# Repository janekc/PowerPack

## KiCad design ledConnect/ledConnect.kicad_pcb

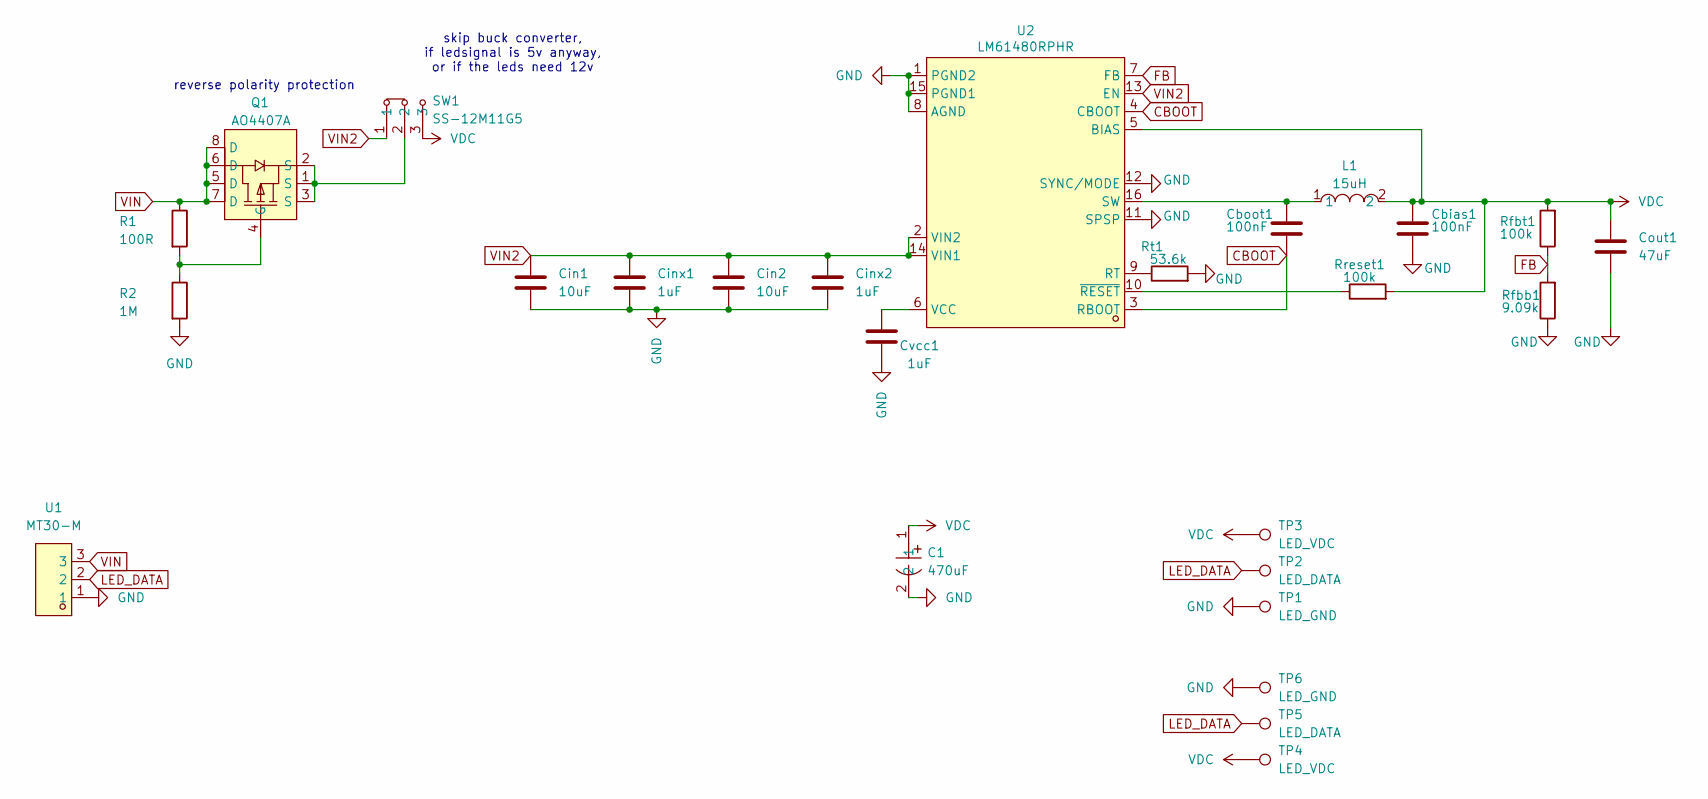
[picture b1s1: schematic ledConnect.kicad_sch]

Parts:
C1: 470uF; CAP-TH_BD10.0-P5.00-D0.6-FD; LCSC Part C2688262
Cbias1: 100nF
Cboot1: 100nF; C_0603_1608Metric_Pad1.08x0.95mm_HandSolder
Cin1, Cin2: 10uF; C_0603_1608Metric_Pad1.08x0.95mm_HandSolder
Cinx1, Cinx2: 1uF; C_0603_1608Metric_Pad1.08x0.95mm_HandSolder
Cout1: 47uF; C_1210_3225Metric_Pad1.33x2.70mm_HandSolder
Cvcc1: 1uF; C_0603_1608Metric_Pad1.08x0.95mm_HandSolder
L1: 15uH; IND-SMD_L13.5-W12.6; LCSC Part C2847574
Q1: AO4407A; SOIC-8_L4.9-W3.9-P1.27-LS6.0-BL; LCSC Part C16072
R1: 100R; R_0603_1608Metric_Pad0.98x0.95mm_HandSolder
R2: 1M; R_0603_1608Metric_Pad0.98x0.95mm_HandSolder
Rfbb1: 9.09k; R_0603_1608Metric_Pad0.98x0.95mm_HandSolder
Rfbt1: 100k; R_0603_1608Metric_Pad0.98x0.95mm_HandSolder
Rreset1: 100k; R_0603_1608Metric_Pad0.98x0.95mm_HandSolder
Rt1: 53.6k; R_0603_1608Metric_Pad0.98x0.95mm_HandSolder
SW1: SS-12M11G5; SW-TH_XKB_SS-12M11XX; LCSC Part C2879839
TP1, TP6: LED_GND; TestPoint_Pad_2.5x2.5mm
TP2, TP5: LED_DATA; TestPoint_Pad_2.5x2.5mm
TP3, TP4: LED_VDC; TestPoint_Pad_2.5x2.5mm
U1: MT30-M; CONN-TH_MT30-M; LCSC Part C99903
U2: LM61480RPHR; VQFN-16_L4.5-W3.5-P0.50-TL_TI_RPH; LCSC Part C3198089

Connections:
CBOOT: Cboot1.2, U2.3 (RBOOT), U2.4 (CBOOT)
FB: Rfbb1.2, Rfbt1.1, U2.7 (FB)
GND: C1.2, Cbias1.2, Cin1.2, Cin2.2, Cinx1.2, Cinx2.2, Cout1.2, Cvcc1.2, R2.2, Rfbb1.1, Rt1.2, TP1.1, TP6.1, U1.1, U2.1 (PGND2), U2.8 (AGND), U2.11 (SPSP), U2.12 (SYNC/MODE), U2.15 (PGND1)
LED_DATA: TP2.1, TP5.1, U1.2
unnamed: Q1.4 (G), R1.2, R2.1
unnamed: Q1.1 (S), Q1.2 (S), Q1.3 (S), SW1.2
unnamed: Rt1.1, U2.9 (RT)
unnamed: Cboot1.1, L1.1, U2.16 (SW)
unnamed: Cvcc1.1, U2.6 (VCC)
unnamed: Rreset1.1, U2.10 (~RESET)
VDC: C1.1, Cbias1.1, Cout1.1, L1.2, Rfbt1.2, Rreset1.2, SW1.3, TP3.1, TP4.1, U2.5 (BIAS)
VIN: Q1.5 (D), Q1.6 (D), Q1.7 (D), Q1.8 (D), R1.1, U1.3
VIN2: Cin1.1, Cin2.1, Cinx1.1, Cinx2.1, SW1.1, U2.2 (VIN2), U2.13 (EN), U2.14 (VIN1)

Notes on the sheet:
skip buck converter, if ledsignal is 5v anyway, or if the leds need 12v
reverse polarity protection

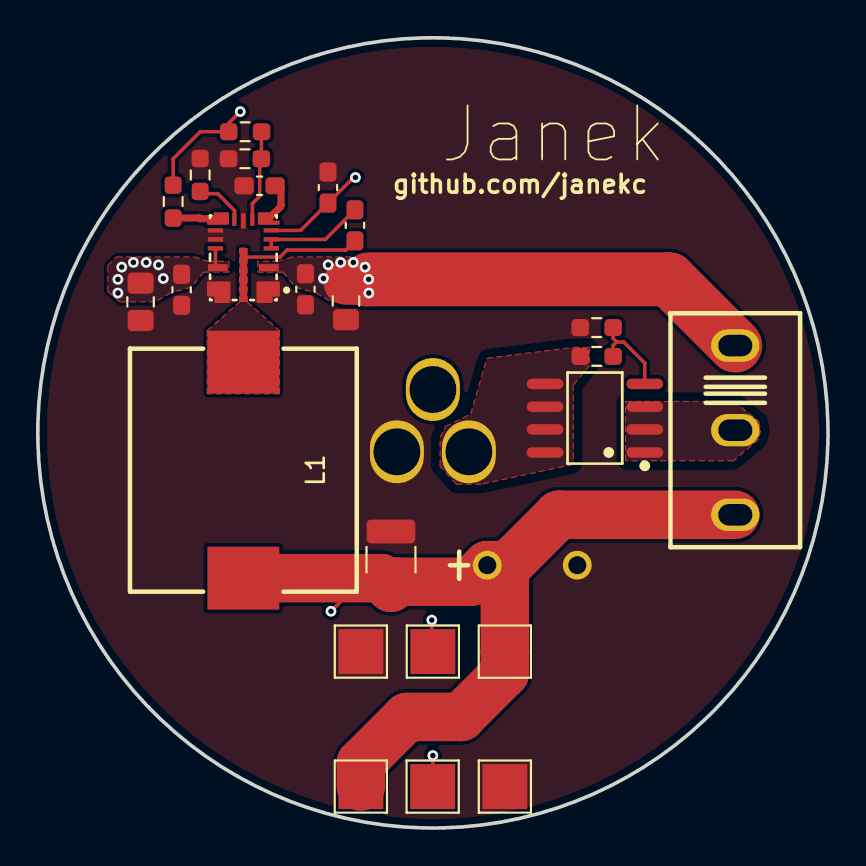
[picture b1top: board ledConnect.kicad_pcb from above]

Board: 4 copper layers, 43.9 x 43.9 mm, 26 parts (1 on the bottom side), 13 nets.

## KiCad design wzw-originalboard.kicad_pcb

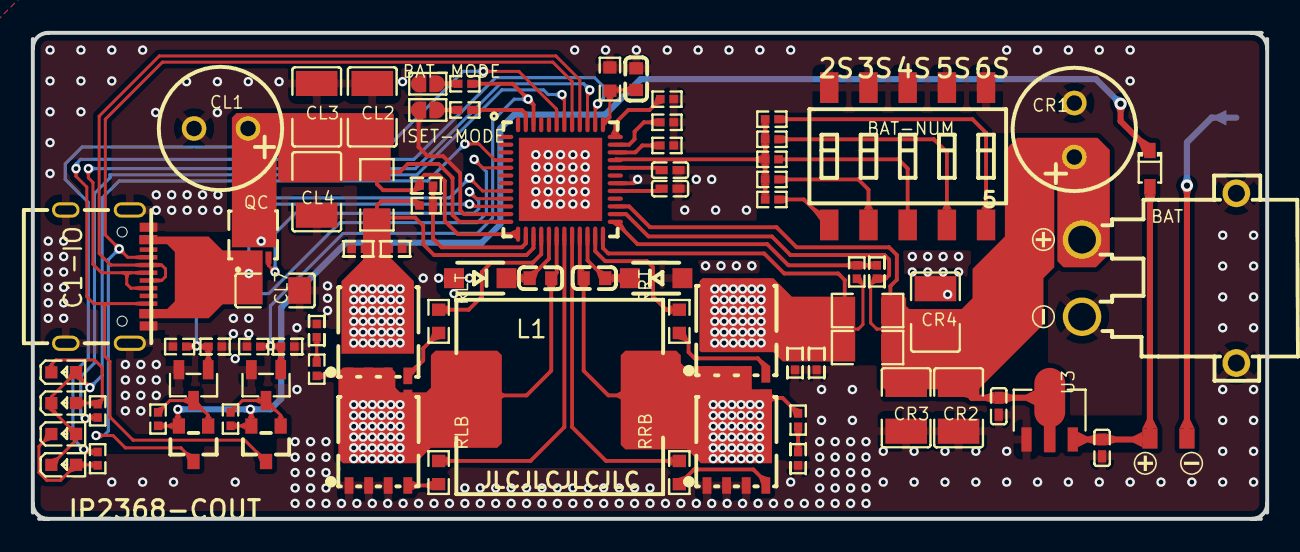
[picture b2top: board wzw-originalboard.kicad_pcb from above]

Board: 2 copper layers, 80.0 x 31.5 mm, 78 parts (0 on the bottom side), 53 nets.

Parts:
2S: 6.2k; R0402
3S: 9.1k; R0402
4S: 13k; R0402
5S: 18k; R0402
6S: 27k; R0402
25%, 50%, 75%, 100%: FC-D1608WD-460H5; LED0603-RD
BAT: XT30PW-M; CONN-TH_XT30PW-M
BAT-MODE: 1k; R0402
BAT-NUM: 5; SW-SMD_DSIC05LS-P
C1-IO: TYPE-C16PIN; USB-C-SMD_TYPE-C16PIN
CBSL: 100nF; C0603
CBSR: 100nF; C0603
CC1, CC2: 1.5nf; C0402
CE1, CE2: 100nF; C0402
CL1: 220uF; CAP-TH_BD8.0-P3.50-D0.6-FD
CL2, CL3, CL4: 22uF; C1210
CL7: 10uF; C1206
CLQ1, CLQ2: 100nF; C0402
CNTC: 100nF; C0603
CR1: 220uF; CAP-TH_BD8.0-P3.50-D0.6-FD
CR2, CR3, CR4: 22uF; C1210
CRQ1, CRQ2: 100nF; C0402
CSC1, CSC2: 1uf; C0402
CVC1, CVC2, CVC3, CVC4: 2.2uF; C0402
D1, D2: SMF30A_C364281; SOD-123FL_L2.6-W1.6-LS3.4-R-FD
DEMK: 1SS355; SOD-323_L1.8-W1.3-LS2.5-RD
ISET-MODE: 1k; R0402
L1: 5.6uH; IND-SMD_L13.4-W12.6
QC: WSD3066DN33; PDFN3333-8_L3.1-W3.2-P0.65-LS3.4-BL
QE1, QE2: 2301; SOT-23_L2.9-W1.3-P1.90-LS2.4-BR
QE3, QE4: 2N7002; SOT-23-3_L2.9-W1.3-P1.90-LS2.4-BR
QLB: 5C670; PDFN-8_L4.9-W5.8-P1.27-LS6.1-BL
QLT: 5C670; PDFN-8_L4.9-W5.8-P1.27-LS6.1-BL
QRB: 5C670; PDFN-8_L4.9-W5.8-P1.27-LS6.1-BL
QRT: 5C670; PDFN-8_L4.9-W5.8-P1.27-LS6.1-BL
R1, R2: 0R; 测试焊盘
RC1, RC2: 2; R0402
RCAPS: 30.9k; R0402
RE1, RE2: 10K; R0402
RE3, RE4: 1M; R0402
RIS: 25k; R0402
RLB: 0Ω; R0603
RLED1, RLED2: 100; R0402
RLT: 0Ω; R0603
RNTC: 10K; R0603
RRB: 0Ω; R0603
RRT: 0Ω; R0603
RSC1, RSC2: 10; R0402
RSCL1: 0.005Ω; R1206
RSCR1, RSCR2: 0.01Ω; R1206
RVS: 10k; R0402
U1: IP2368
U3: ME6203A50PG; SOT-89_L4.5-W2.5-P1.50-LS4.2-BR

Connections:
2S_2: 2S.2, BAT-NUM.1
3S_2: 3S.2, BAT-NUM.2
4S_2: 4S.2, BAT-NUM.3
5S_2: 5S.2, BAT-NUM.4
6S_2: 6S.2, BAT-NUM.5
BAT-MODE: BAT-MODE.1, CE2.2, QE4.1, RE4.2, U1.46
BAT-MODE_2: BAT-MODE.2, R2.1
CC1_2: CC1.2, RC1.1
CC2_2: CC2.2, RC2.1
CIO1_CC1: C1-IO.A5, QE2.3, U1.41
CIO1_CC2: C1-IO.B5, QE1.3, U1.38
CIO1_DM: C1-IO.A7, C1-IO.B7, U1.40
CIO1_DP: C1-IO.A6, C1-IO.B6, U1.39
DEMK_2: CVC3.2, DEMK.2, U3.3
GND: BAT.1, BAT.3, BAT.4, BAT-NUM.6, BAT-NUM.7, BAT-NUM.8, BAT-NUM.9, BAT-NUM.10, C1-IO.1, C1-IO.2, C1-IO.3, C1-IO.4, C1-IO.A1B12, C1-IO.B1A12, CC1.1, CC2.1, CE1.1, CE2.1, CL1.2, CL2.1, CL3.1, CL4.1, CL7.1, CLQ1.1, CLQ2.1, CNTC.1, CR1.2, CR2.1, CR3.1, CR4.1, CRQ1.1, CRQ2.1, CVC1.1, CVC2.1, CVC3.1, CVC4.1, D1.2, D2.2, QE3.2, QE4.2, QLB.1, QLB.2, QLB.3, QRB.1, QRB.2, QRB.3, R1.2, R2.2, RCAPS.2, RE3.2, RE4.1, RIS.2, RNTC.2, RVS.2, U1.11, U1.30, U1.49, U3.1
HLED: CE1.2, QE3.1, RE3.1, U1.5
ISET-MODE_2: ISET-MODE.2, R1.1
QE1_1: QE1.1, QE4.3, RE1.1
QE2_1: QE2.1, QE3.3, RE2.1
QE2_2: DEMK.1, QE1.2, QE2.2, RE1.2, RE2.2
QLB_4: QLB.4, RLB.1
QLT_4: QLT.4, RLT.1
QRB_4: QRB.4, RRB.1
QRT_4: QRT.4, RRT.1
RLED1_2: 25%.2, 50%.1, RLED1.2
RLED2_2: 75%.2, 100%.1, RLED2.2
U1_4: 25%.1, 50%.2, 75%.1, 100%.2, U1.4
U1_9: QC.4, U1.9
U1_14: CSC1.2, RSC1.1, U1.14
U1_15: CLQ1.2, CLQ2.2, QLT.5, QLT.6, QLT.7, QLT.8, QLT.9, RSC1.2, RSCL1.2, U1.15
U1_16: RLT.2, U1.16
U1_17: CBSL.2, D1.1, U1.17
U1_18: CBSL.1, L1.1, QLB.5, QLB.6, QLB.7, QLB.8, QLB.9, QLT.1, QLT.2, QLT.3, RC1.2, U1.18
U1_19: RLB.2, U1.19
U1_20: RRB.2, U1.20
U1_21: CBSR.1, L1.2, QRB.5, QRB.6, QRB.7, QRB.8, QRB.9, QRT.1, QRT.2, QRT.3, RC2.2, U1.21
U1_22: CBSR.2, D2.1, U1.22
U1_23: RRT.2, U1.23
U1_24: CRQ1.2, CRQ2.2, QRT.5, QRT.6, QRT.7, QRT.8, QRT.9, RSC2.2, RSCR1.1, RSCR2.1, U1.24
U1_25: CSC2.2, RSC2.1, U1.25
U1_29: CVC1.2, U1.29
U1_32: CVC2.2, U1.32
U1_33: 2S.1, 3S.1, 4S.1, 5S.1, 6S.1, U1.33
U1_34: RCAPS.1, U1.34
U1_35: RVS.1, U1.35
U1_36: RIS.1, U1.36
U1_37: CNTC.2, RNTC.1, U1.37
U1_42: RLED2.1, U1.42
U1_43: RLED1.1, U1.43
U1_47: ISET-MODE.1, U1.47
VBUSL_CIO1: C1-IO.A4B9, C1-IO.B4A9, CL7.2, QC.1, QC.2, QC.3, U1.8
VBUSL_SOURCE: CL1.1, CL2.2, CL3.2, CL4.2, CSC1.1, QC.5, QC.6, QC.7, QC.8, QC.9, RSCL1.1, U1.10, U1.12, U1.13
VBUSR_SOURCE: BAT.2, CR1.1, CR2.2, CR3.2, CR4.2, CSC2.1, CVC4.2, RSCR1.2, RSCR2.2, U1.26, U1.27, U3.2
